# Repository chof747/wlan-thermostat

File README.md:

## wlan-thermostat
Wireless Thermostats for elecrically triggerd heatings

This is the front panel of a wireless triggered heating which can be connected to a second board that contains the 
power supply and a relais capeable of switching the required electrical load. The front panel is designed to be
attached in a perpendicular way to the back part.

### Elements:

- An ESP8266-12F module containing the microcontroller, Flash
- A SHT40 temperature and humidity sensor
- A rotary encoder for input
- A SSD1306 OLED display for output
- Voltage regulator to regulate the 5V from the back board to 3v3 for the ESP8266 
- Programming logic and headers
- Headers to connect to the back board for power control and relay switching

## Used Parts:

## Revision History:

- **v1.0**: Initial version (Produced: 12.06.2023; First assembled: 29.06.2023)
- **v1.1**: Fixing after component testin (Produced: 15.07.2023; First assembled: 31.07.2023 / Frontend)
   1. Frontend:
     - Fixing of strapping pins of ESP-12F
     - Fixing of thermocoupling between ESP-12F and the temperature sensor
     - Introduction of UMH3N chip to replace two transistors + two resistors for the auto-reset circuit
     - Introduced resistor array to manage strapping pins
     - Switching of pins as follows:
         - Rotary Encoder Button now GPIO0 (doubling as a fallback mode for programming)
         - Relay pin: GPIO13

   2. Backend
     - Fixed orientation of Relay Footprint
     - Fixed size of footprint for optocoppler
     - Changed pinheaders for frontend connection from smd to throughole
     - Rearranged board placing to manage changed footprints
- **v1.2**: Alternate version without (exposed) ground panel at the back of the frontend thermo sensor
- **v1.3b**: Moved the temperature sensor to a sidearm sticking out of the board (produced 18.09.2023)
- **v1.2 (backend)**: Corrected pin order of transistor switching relay (Produced: 15.10.2023)

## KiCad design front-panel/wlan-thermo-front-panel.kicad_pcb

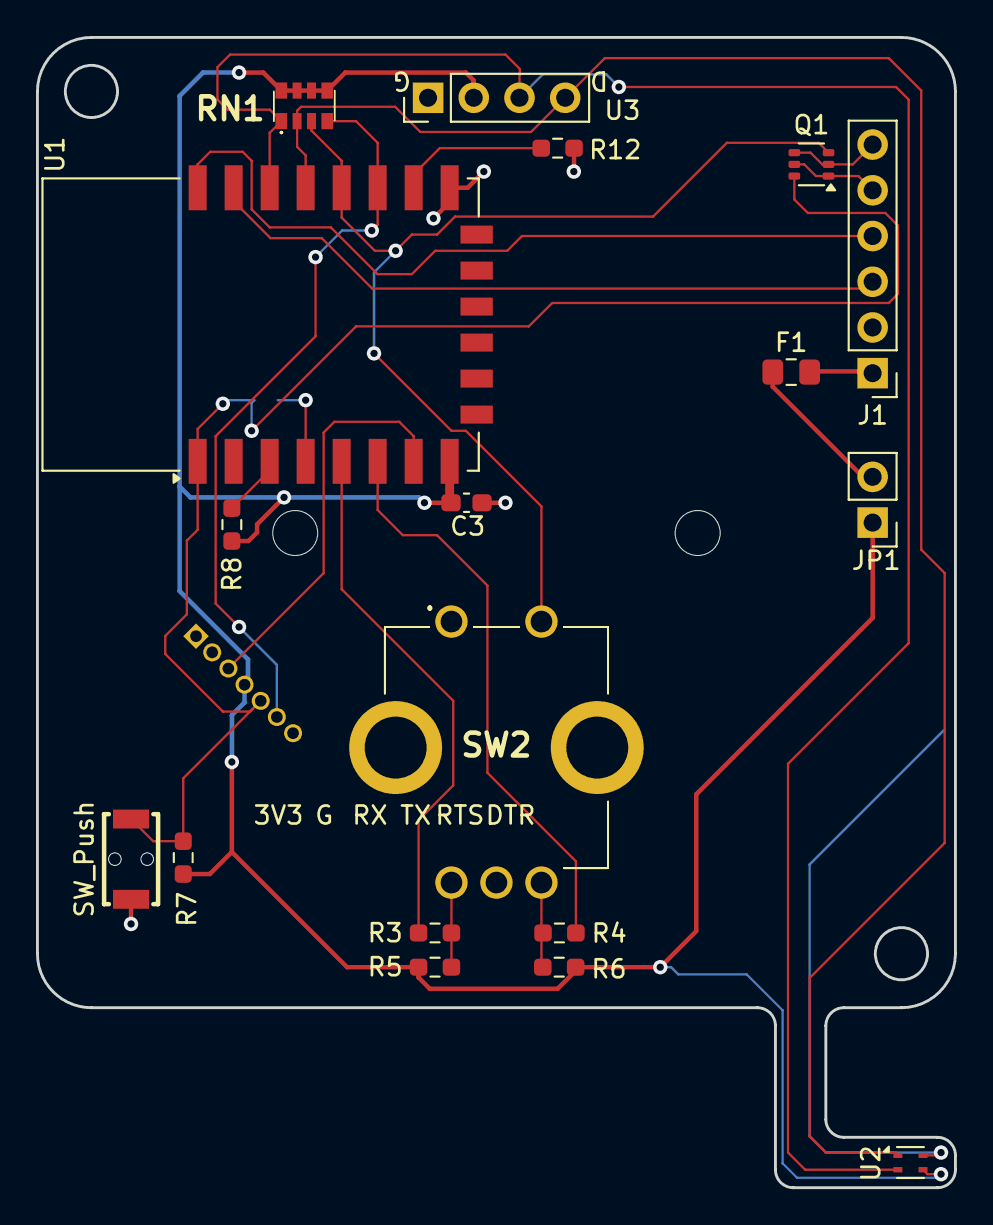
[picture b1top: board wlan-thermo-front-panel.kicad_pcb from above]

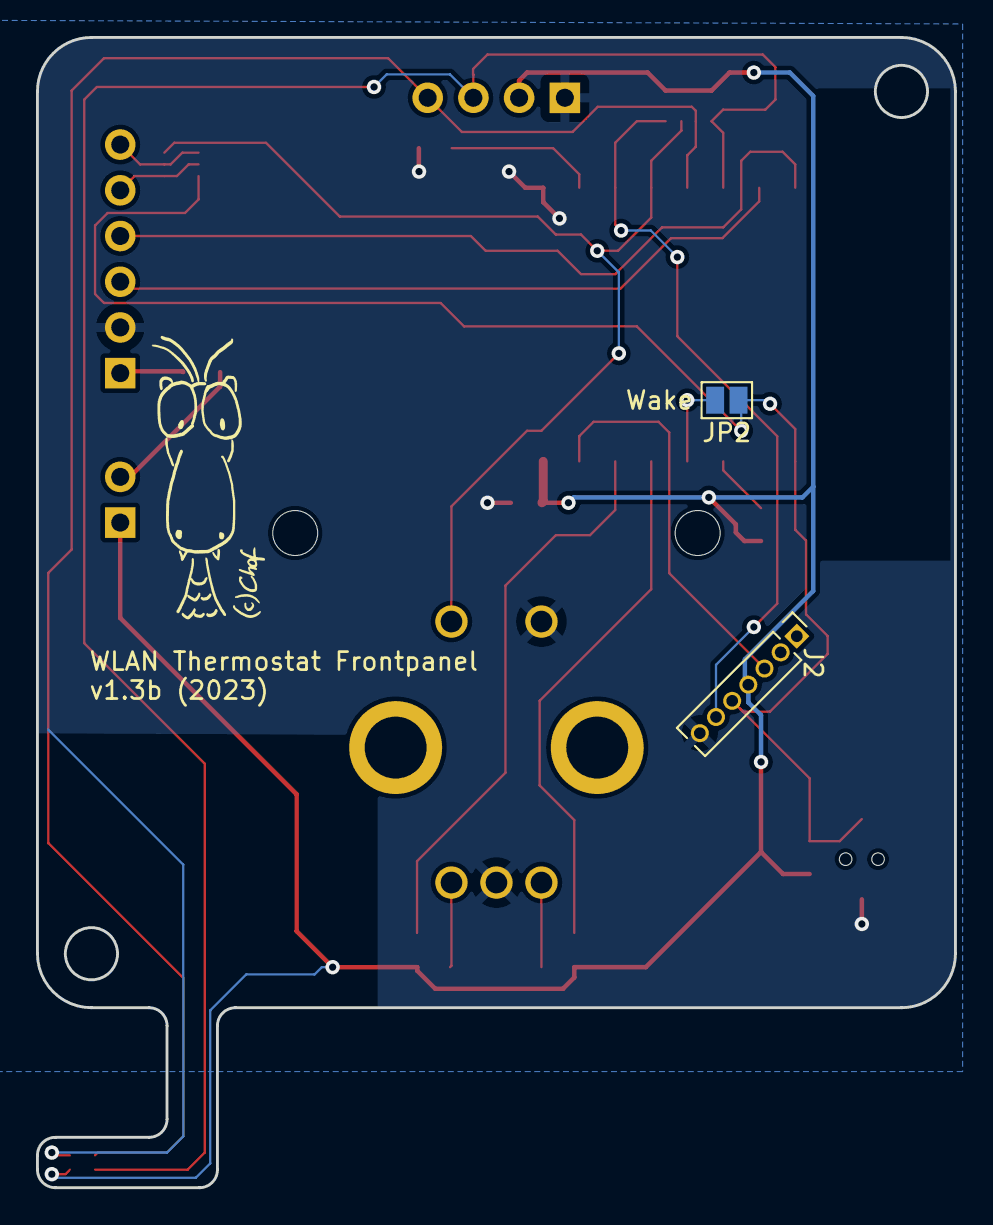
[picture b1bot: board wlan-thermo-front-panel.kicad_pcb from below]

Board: 2 copper layers, 51.0 x 63.9 mm, 20 parts (2 on the bottom side), 21 nets.

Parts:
C3: 10uF; C_0603_1608Metric_Pad1.08x0.95mm_HandSolder
F1: Fuse; Fuse_0805_2012Metric_Pad1.15x1.40mm_HandSolder
J1: PROG_HDR; PinHeader_1x06_P2.54mm_Vertical
J2: Device Connector; PinHeader_1x07_P1.27mm_Vertical
JP1: PWR_PROG; PinHeader_1x02_P2.54mm_Vertical
JP2: Wake; SolderJumper-2_P1.3mm_Open_Pad1.0x1.5mm
Q1: UMH3N; SOT-363_SC-70-6
R3, R4: 1k; R_0603_1608Metric_Pad0.98x0.95mm_HandSolder
R5, R6: 22k; R_0603_1608Metric_Pad0.98x0.95mm_HandSolder
R7, R8, R12: 10k; R_0603_1608Metric_Pad0.98x0.95mm_HandSolder
RN1: 10k; YC164JR07220RL
SW1: SW_Push; KEY-SMD_L3.9-W3.0-LS5.0-EH
SW2: RotaryEncoder_Switch; PEC12R3120FS0012
U1: ESP-12F; ESP-12E
U2: SHT4x; Sensirion_DFN-4_1.5x1.5mm_P0.8mm_SHT4x_NoCentralPad
U3: SSD1306; AZ Delivery SS1306 OLED

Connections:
+3V3: C3.1, J2.4, JP1.1 (A), R5.2, R6.2, R7.1, R8.1, RN1.5, RN1.6, RN1.7, RN1.8, U1.8 (VCC), U2.3 (VDD), U3.2 (VCC)
/3v3PROG: F1.2, J1.1
/3v3PROG_SAVE: F1.1, JP1.2 (B)
DTR: J1.6, Q1.2 (B1), Q1.4 (E2)
GND: C3.2, J1.2, J2.7, R12.2, SW1.2, SW2.1 (COM), SW2.C1 (COMMON), U1.15 (GND), U2.4 (VSS), U3.1 (GND)
GPIO2_RELAY: J2.6, RN1.4, U1.17 (GPIO2)
GPIO3_RX: J1.3, U1.21 (GPIO3/RXD)
GPIO4_SDA: RN1.2, U1.19 (GPIO4), U2.1 (SDA), U3.4 (SDA)
GPIO4_TX: J1.4, U1.22 (GPIO1/TXD)
GPIO5_SCL: RN1.1, U1.20 (GPIO5), U2.2 (SCL), U3.3 (SCL)
GPIO12_RENDAT: R4.1, U1.6 (GPIO12)
GPIO13_RX1: J2.3, U1.7 (GPIO13)
GPIO14_RENCLK: R3.1, U1.5 (GPIO14)
GPIO16_WAKE: JP2.2 (B), U1.4 (GPIO16)
unnamed: R3.2, R5.1, SW2.A1 (CHANNEL_A)
unnamed: R4.2, R6.1, SW2.B1 (CHANNEL_B)
unnamed: R8.2, U1.3 (EN)
unnamed: R12.1, U1.16 (GPIO15)
RTS: J1.5, Q1.1 (E1), Q1.5 (B2)
~GPIO0_RENBTN_FLASH: Q1.3 (C2), RN1.3, SW2.2 (NO), U1.18 (GPIO0)
~RESET: J2.5, JP2.1 (A), Q1.6 (C1), R7.2, SW1.1, U1.1 (~RST)

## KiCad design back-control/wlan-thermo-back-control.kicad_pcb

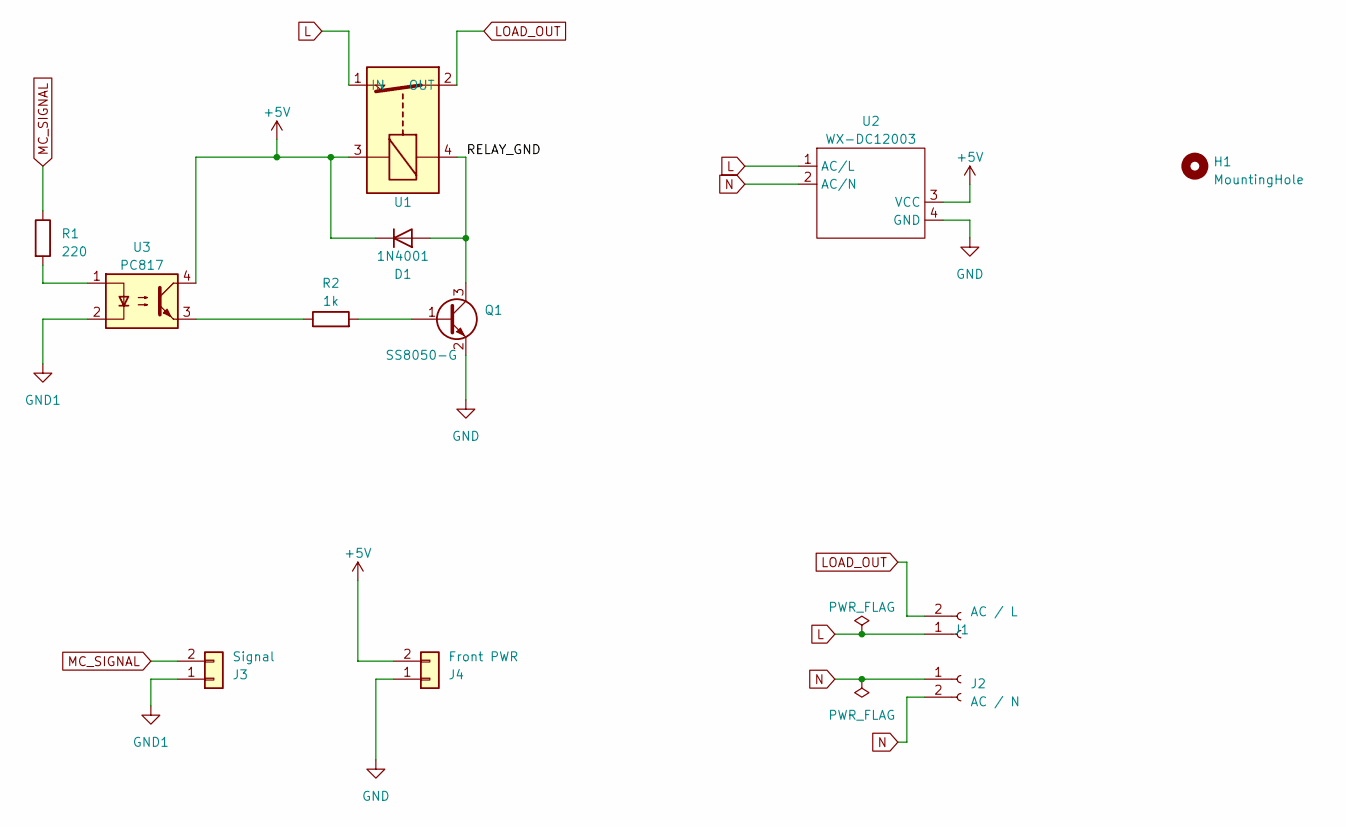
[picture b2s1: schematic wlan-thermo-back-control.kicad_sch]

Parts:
D1: 1N4001; D_DO-41_SOD81_P10.16mm_Horizontal
H1: MountingHole; MountingHole_3.2mm_M3
J1: AC / L; TerminalBlock_2_P10.16mm
J2: AC / N; TerminalBlock_bornier-2_P5.08mm
J3: Signal; PinSocket_1x02_P2.54mm_Vertical
J4: Front PWR; PinSocket_1x02_P2.54mm_Vertical
Q1: SS8050-G; SOT-23
R1: 220; R_0603_1608Metric_Pad0.98x0.95mm_HandSolder
R2: 1k; R_0603_1608Metric_Pad0.98x0.95mm_HandSolder
U1: BS6-5-AST-P
U2: WX-DC12003
U3: PC817; DIP-4_W7.62mm

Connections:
+5V: D1.1 (K), J4.2, U1.3, U2.3 (VCC), U3.4
/RELAY_GND: D1.2 (A), Q1.3 (C), U1.4
GND: J4.1, Q1.2 (E), U2.4 (GND)
GND1: J3.1, U3.2
L: J1.1, U1.1 (IN), U2.1 (AC/L)
LOAD_OUT: J1.2, U1.2 (OUT)
MC_SIGNAL: J3.2, R1.1
N: J2.1, J2.2, U2.2 (AC/N)
unnamed: Q1.1 (B), R2.2
unnamed: R1.2, U3.1
unnamed: R2.1, U3.3

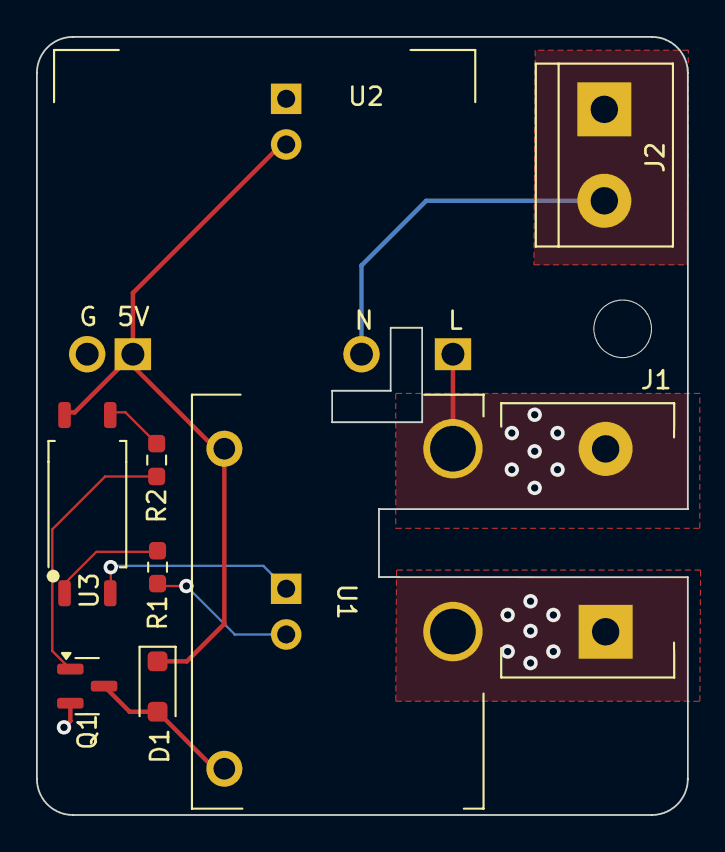
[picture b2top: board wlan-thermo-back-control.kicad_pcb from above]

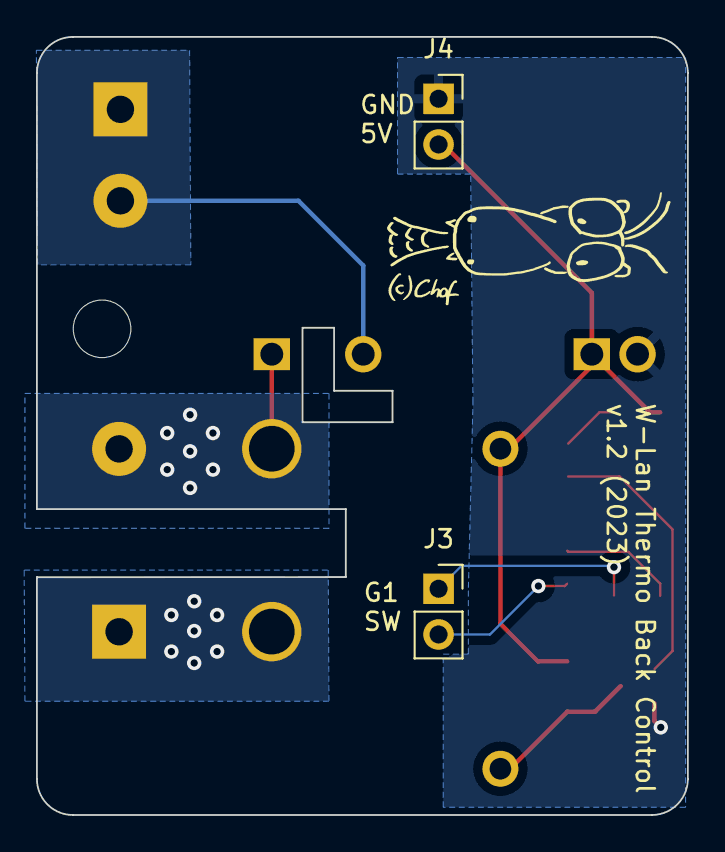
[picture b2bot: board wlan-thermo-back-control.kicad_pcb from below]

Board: 2 copper layers, 36.2 x 43.2 mm, 12 parts (2 on the bottom side), 11 nets.

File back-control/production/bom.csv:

Designator,Footprint,Quantity,Value,LCSC Part #
D1,D_SOD-123F,1,1N4001,
J1,TerminalBlock_bornier-2_P5.08mm,1,AC / L,
J2,TerminalBlock_bornier-2_P5.08mm,1,AC / N,
J3,PinSocket_1x02_P2.54mm_Vertical,1,Signal,
J4,PinSocket_1x02_P2.54mm_Vertical,1,Front PWR,
Q1,SOT-23,1,SS8050-G,
R1,R_0603_1608Metric_Pad0.98x0.95mm_HandSolder,1,220,
R2,R_0603_1608Metric_Pad0.98x0.95mm_HandSolder,1,1k,
U1,BS6-5-AST-P,1,~,
U2,WX-DC12003,1,WX-DC12003,
U3,SOP-4_3.8x4.1mm_P2.54mm,1,PC817,

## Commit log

2023-04-27 initial setup
2023-04-27 Updated template for KiCAD 7
2023-05-02 Initial board version
2023-05-04 Changed board size to fit into standard frame for power outlet
2023-05-11 created subdirs for front and back panel. First version of back panel
2023-05-14 First version fitting together
2023-05-31 Corrected traces and spacings for assembly
2023-07-02 Fixed strapping pins for booting and loading
2023-07-04 Decoupled sht40 from main ground plane
    In order to measure the ambient temperature and not the board one
    the following measures where taken:
    - Remove the ground plane from the area around the sensor
    - Turn all connections around so that a cut-out can be drawn around the component
    - Expose the copper on the back of the sensor's ground plane as additional heat disipation
2023-07-08 changed minimum copper clearance
2023-07-08 Changed strapping pins to resistor network
2023-07-09 Use UMH3N chip for autorestart cycle
    - Removed Q1/Q2 and the two 10k resistors and replace it with UMH3N for autoreset
    - Changed footprint of fuse to 0804
    - Reorganised board to be smaller to fit into casing of existing wall switch
2023-07-10 Corrected wrongly placed footprint for relay
2023-07-12 removed solder mask over backside of contacts
2023-07-12 Changed relay pin to avoid on on flash and boot
    - Change relay pin to GPIO 13
    - Change Rotary encoder pin to GPIO0 (also pulled up and provides extra feature: Rotary button works as flash button)
2023-07-15 Revised optocopler footprint
2023-07-15 Redid whole for creeping protection of power supply
    - Changed frontend connectors also to throughole pins
2023-07-15 Merging of first revision round after component testing
2023-07-31 New 3D Step file
2023-08-19 Removed (exposed) ground plane from sensor area (rev 1.2)
2023-08-19 Ignored resources directory
2023-09-18 external version of temp sensor
2023-09-18 Version 1.3b with side arm for temp sensor
2023-09-18 Added ordering date for version 1.3b
2023-10-15 Correcrted relay switching transistor pins
2024-02-10 Added board outlines
2024-03-14 upgrade to KiCad 8.0
2024-12-26 removed gerber artifacts
2024-12-26 removed backend board as it is not needed in this version
2024-12-26 adjusted gitignore for auto_saved_files
2024-12-26 crc checked first version of board with backend shelly
2025-03-18 minor changes
2025-03-18 issue description of temp issue
2025-03-20 Changed position of temp sensor
    Moved temp sensor to the bottom
    Replaced and rerouted other components
